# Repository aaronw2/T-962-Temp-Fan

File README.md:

This board provides support for up to 4 K-type temperature probes as
well as fan PWM support and a USB to serial interface to enhance the
T-962 reflow oven. This also incorporates support for pulse-width modulating
the fan and providing a USB to serial interface for programming.

The firmware source code can be found at
https://github.com/UnifiedEngineering/T-962-improvements

Instructions on how to flash the firmware can be found at
https://github.com/UnifiedEngineering/T-962-improvements/wiki/Flashing-the-LPC21xx-controller

All of the improvements are described on
https://hackaday.com/2014/11/27/improving-the-t-962-reflow-oven/

Note that RXD0 pin on this board must be connected to the TX pin on the T-962
controller and that the TXD0 pin must be connected to the RX pin on the T-962.

If you do not wish for the USB support, do not install the following components:
C6, C9, C10, D1-D3, J8, J10, R3-R9, U7

If you do not need the UART indicators do not install D2, D3, R8 or R9.

If you only want the two internal temperature sensors, do not install
C8, C11, C12, C13, U4 or U6 and replace J2 with a 4 terminal version of the
connector.

If external buttons are added for programming, they can be connected to J9 and
switches SW1 and SW2 do not need to be installed.

Use either the USB-C or J10 for connecting USB.

Connectors:

J1: Connect to T962 controller board
1: DQ
2: FAN_PWM
3: GND

J2: Thermocouple connector
1: T3+
2: T3-
3: T2+
4: T2-
5: T1+
6: T1-
7: T0+
8: T0-

J3: 12V in
1: GND
2: +12V

J4: +3V out
1: GND
2: +3V

J5: Fan out
1: PWM (GND)
2: +12V

J6: +12V out
1: GND
2: +12V

J7: Programming Header, connect to T962 controller board header
1: N_ISP
2: N_RST
3: RX
4: TX
5: GND

Hook up either J8 or J10, not both

J8: USB-C

J9: N_ISP and N_RST for external buttons
1: N_RST
2: GND
3: N_ISP

J10: USB
1: GND
2: D+
3: D-
4: +5V

BOM:
QTY Ref
5   C1,C4,C8,C10,C12: 0.1uf X7R 0603
4   C2,C5,C11,C13 0.01uF X7R 0603
1   C3 1uF X7R 0603
1   C6,C9 4.7uF X7R 0603
1   D1: ST Microelectronics USBLC6-2SC6
1   D2: Würth Elektronik Red 0603 LED 150060RS75000
1   D3: Würth Elektronik Green 0603 LED 150060VS75020
1   J2: TE 282834-8
1   J3, J5, J6: JST XH-B02B-XH-AM
1   J8: GTC USB4105-GF-A-060 USB-C connector
1   Q1: Infineon BSS214NWH6327XTSA1
1   R1: 4.7K 0603
1   R2: 100K 0603
1   R3: 1K 0603
1   R4: 24K 0603
1   R5: 47.5K 0603
2   R6,R7: 5.1K 0603
2   R8,R9: 560 0603
2   S1, S2: C&K KMR221GLFS LFS
4   U1, U3, U4, U6: Maxim MAX31850KATB+
1   U2: ST Microelectronics LD1117S33CTR
1   U5: Silicon Labs CP2104-F03-GM

All parts can be found at Digikey. The BOM provides both the manufacturer and
Digikey part numbers as well as links to all of the parts on Digikey.  Feel
free to substitute any of the resistors but use 5% or better or any of the
capacitors (use X7R temperature coefficient and make sure the voltages are
appropriate).  There are several variations of the KMR2 C&K buttons, the only
difference is the force required and current.  Any KMR2 button can be used.

Similarly, feel free to substitute LEDs, but the rated voltage should be
2V or lower. If a 3V LED is used you may need to reduce the resistors from
560 owhms to 100 ohms.

The fan mosfet is rated for 1.5A.

The board is designed with Oshpark.com in mind for manufacturing, but most
decent board houses should be able to make these without any difficulty.

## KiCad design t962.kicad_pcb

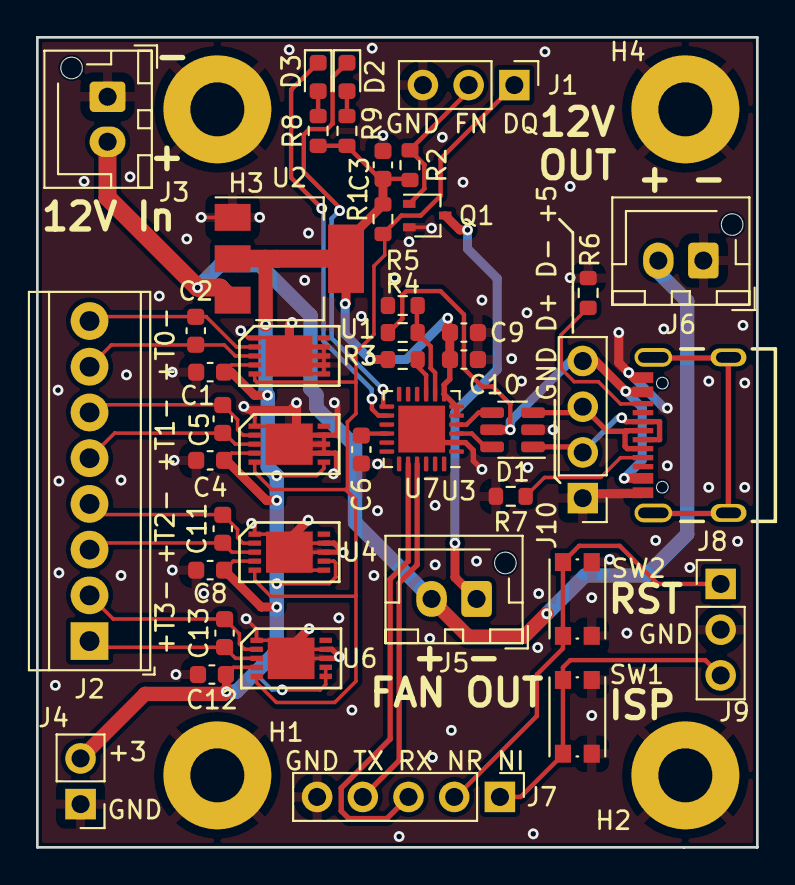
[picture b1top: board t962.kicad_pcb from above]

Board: 2 copper layers, 40.0 x 45.0 mm, 47 parts (0 on the bottom side), 32 nets.

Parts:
C1, C4, C8, C10, C12: 0.1uF; C_0603_1608Metric
C2, C5, C11, C13: 0.01uF; C_0603_1608Metric
C3: 1uF; C_0603_1608Metric
C6, C9: 4.7uF; C_0603_1608Metric
D1: USBLC6-2SC6; SOT-23-6
D2: Red; LED_0603_1608Metric
D3: Green; LED_0603_1608Metric
H1, H2, H3, H4: MountingHole_Pad; MountingHole_3mm_Pad
J1: Conn_01x03; PinHeader_1x03_P2.54mm_Vertical
J2: TE 282834-8; TerminalBlock_TE_282834-8_1x08_P2.54mm_Horizontal
J3, J5, J6: JST XH-B02B-XH-AM; JST_XH_B2B-XH-AM_1x02_P2.50mm_Vertical
J4: Conn_01x02_Male; PinHeader_1x02_P2.54mm_Vertical
J7: 2.54mm pin header; PinHeader_1x05_P2.54mm_Vertical
J8: USB_C_Receptacle_USB2.0; GCT_USB4105-GF-A
J9: Conn_01x03_Male; PinHeader_1x03_P2.54mm_Vertical
J10: Conn_01x04; PinHeader_1x04_P2.54mm_Vertical
Q1: BSS214NW; SOT-323_SC-70
R1: 4.7K; R_0603_1608Metric
R2: 100K; R_0603_1608Metric
R3: 1K; R_0603_1608Metric
R4: 24K; R_0603_1608Metric
R5: 47.5K; R_0603_1608Metric
R6, R7: 5.1K; R_0603_1608Metric
R8, R9: 560; R_0603_1608Metric
SW1, SW2: SW_SPST_KMR2
U1, U3, U4, U6: MAX31850KATB+; TDFN-10_3x4mm_P0.5mm
U2: LD1117S33CTR; SOT-223
U7: CP2104; QFN-24-1EP_4x4mm_P0.5mm_EP2.6x2.6mm

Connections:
+3V3: C1.2, C3.1, C4.2, C8.2, C9.1, C10.1, C12.2, J4.2, R1.1, R2.1, R3.1, R8.1, R9.1, U1.4 (VDD), U2.2 (VOUT), U2.4 (VOUT), U3.4 (VDD), U3.6 (AD0), U4.4 (VDD), U4.7 (AD1), U6.4 (VDD), U6.6 (AD0), U6.7 (AD1), U7.5 (VIO), U7.6 (VDD), U7.7 (REGIN)
+5V: D1.5, J8.A4 (VBUS), J8.B9 (VBUS), J10.4, R4.1
+12V: J3.2, J5.2, J6.2, U2.3 (VIN)
/CC1: J8.A5 (CC1), R7.1
/CC2: J8.B5 (CC2), R6.1
/D+: D1.1, J8.A6 (D+), J8.B6 (D+), J10.2
/D-: D1.3, J8.A7 (D-), J8.B7 (D-), J10.3
/DQ: J1.1, R1.2, U1.5 (DQ), U3.5 (DQ), U4.5 (DQ), U6.5 (DQ)
/FAN_PWM: J1.2, Q1.1 (G), R2.2
/FAN_PWM_OUT: J5.1, Q1.3 (D)
/N_ISP: J7.1, J9.3, SW1.1
/N_RST: J7.2, J9.1, SW2.1
/P_D+: D1.6, U7.3 (D+)
/P_D-: D1.4, U7.4 (D-)
/RXD0: J7.3, U7.20 (RXD)
/RX_LED: D2.1 (K), U7.13 (RXT/GPIO.1)
/T0+: C2.1, J2.7, U1.3 (T+)
/T0-: C2.2, J2.8, U1.2 (T-)
/T1+: C5.1, J2.5, U3.3 (T+)
/T1-: C5.2, J2.6, U3.2 (T-)
/T2+: C11.1, J2.3, U4.3 (T+)
/T2-: C11.2, J2.4, U4.2 (T-)
/T3+: C13.1, J2.1, U6.3 (T+)
/T3-: C13.2, J2.2, U6.2 (T-)
/TXD0: J7.4, U7.21 (TXD)
/TX_LED: D3.1 (K), U7.14 (TXT/GPIO.0)
GND: C1.1, C3.2, C4.1, C6.2, C8.1, C9.2, C10.2, C12.1, D1.2, H1.1, H2.1, H3.1, H4.1, J1.3, J3.1, J4.1, J6.1, J7.5, J8.A1 (GND), J8.B12 (GND), J9.2, J10.1, Q1.2 (S), R5.2, R6.2, R7.2, SW1.2 (S), SW2.2 (S), U1.1 (GND), U1.6 (AD0), U1.7 (AD1), U1.8 (AD2), U1.9 (AD3), U1.11 (GND), U2.1 (GND), U3.1 (GND), U3.7 (AD1), U3.8 (AD2), U3.9 (AD3), U3.11 (GND), U4.1 (GND), U4.6 (AD0), U4.8 (AD2), U4.9 (AD3), U4.11 (GND), U6.1 (GND), U6.8 (AD2), U6.9 (AD3), U6.11 (GND), U7.2 (GND), U7.25 (GND)
unnamed: D2.2 (A), R9.2
unnamed: D3.2 (A), R8.2
unnamed: R4.2, R5.1, U7.8 (VBUS)
unnamed: C6.1, U7.16 (VPP)
unnamed: R3.2, U7.9 (~RST)

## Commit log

2018-11-17 Initial commit.
2018-11-18 Added more part number information.
2018-12-03 Fixed 12V connectors and USB to serial
    This swaps +12 and GND on the 12V and fan connectors and adds a second
    12v connector for bypassing the fan control if desired. Additionally,
    the SI2102N is now powered from the 3.3V supply instead of the USB bus.
    Updated to revision 1.1.
2018-12-03 Updated BOM
2018-12-03 Added gerber files.
2019-01-05 This fixes the VIO input so it is properly powered. Additionally, the footprint for the USBLC6-2SC6 has been fixed to a SOT23-6 which is a bigger footprint than the SOT666 that was there.
2019-01-26 Fixed solder mask clearance.
2019-02-06 Fixed solder mask again and included pictures.
2019-02-09 Fixed pad mask clearance.
2019-02-09 Added PDF of schematic.
2019-02-09 Fixed solder mask min width again.
2019-02-09 Updated gerbers to match.
2019-03-27 Swap TX/RX and add connector to expose RST and NI
    TX and RX were swapped from what they should be. This
    fixes that. Additionally, J9 was added so that external
    buttons can be added for NI and RST.
2019-03-27 Forgot to save changes for rev 1.2.3
2023-05-24 Modified design for USB-C. This also switches the pins for rx and tx with the UART and changes the CP2102 to a CP2104. UART indicator LEDs were also added and various issues were cleaned up on the PC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

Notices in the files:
t962.kicad_pcb:
Copyright © 2018 by Aaron Williams
